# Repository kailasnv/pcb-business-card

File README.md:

# PCB Business Card

A creditcard sized custom PCB that doubles as a contact card and an interactive embedded demo. Designed from scratch, No dev board, no modules, bare chip bring up on a custom 2 layer board.

---

## What it does

| Mode | Trigger | Description |
|---|---|---|
| **Scroll** | Idle | Scrolls name and contact details across the 8×8 LED matrix |
| **Flappy Bird** | Button press | Classic Flappy Bird on an 8×8 grid |
| **Ball** | Tilt card | 1-pixel ball rolls around the matrix responding to physical tilt |

---

## Hardware

| Component | Part | Purpose |
|---|---|---|
| MCU | STM32G071RBT6 (LQFP-64) | Main processor, Cortex-M0+ @ 64MHz |
| LED Driver | MAX7219 (SOIC-24) | Drives 8×8 LED matrix over SPI |
| Display | 8×8 red LED matrix (0603 LEDs) | Output display |
| Accelerometer | IIS2DLPC (LGA-12) | 3-axis tilt sensing over I²C |
| Charger | TP4056 (SOP-8) | LiPo charging via USB-C |
| Regulator | MCP1700 | 3.3V LDO from LiPo |
| Power | 3.7V 1500mAh LiPo | Battery |
| Input | SMD tactile switch (3×6mm) | Game button |
| Connector | USB-C (16-pin SMD) | Charging input |

---

## Schematic overview

Five sub-circuits:
- **Power** — USB-C → TP4056 → LiPo → MCP1700 → 3.3V rail
- **MCU** — STM32G071RB with decoupling, BOOT0 pull-down, SWD pads
- **LED matrix** — MAX7219 driven over SPI, 64× 0603 LEDs in 8×8 grid
- **Accelerometer** — IIS2DLPC over I²C with additional INT1 interrupt line to MCU
- **Input** — Tactile button + 4-pad SWD debug port

---

###### Firmware (in progress)

---

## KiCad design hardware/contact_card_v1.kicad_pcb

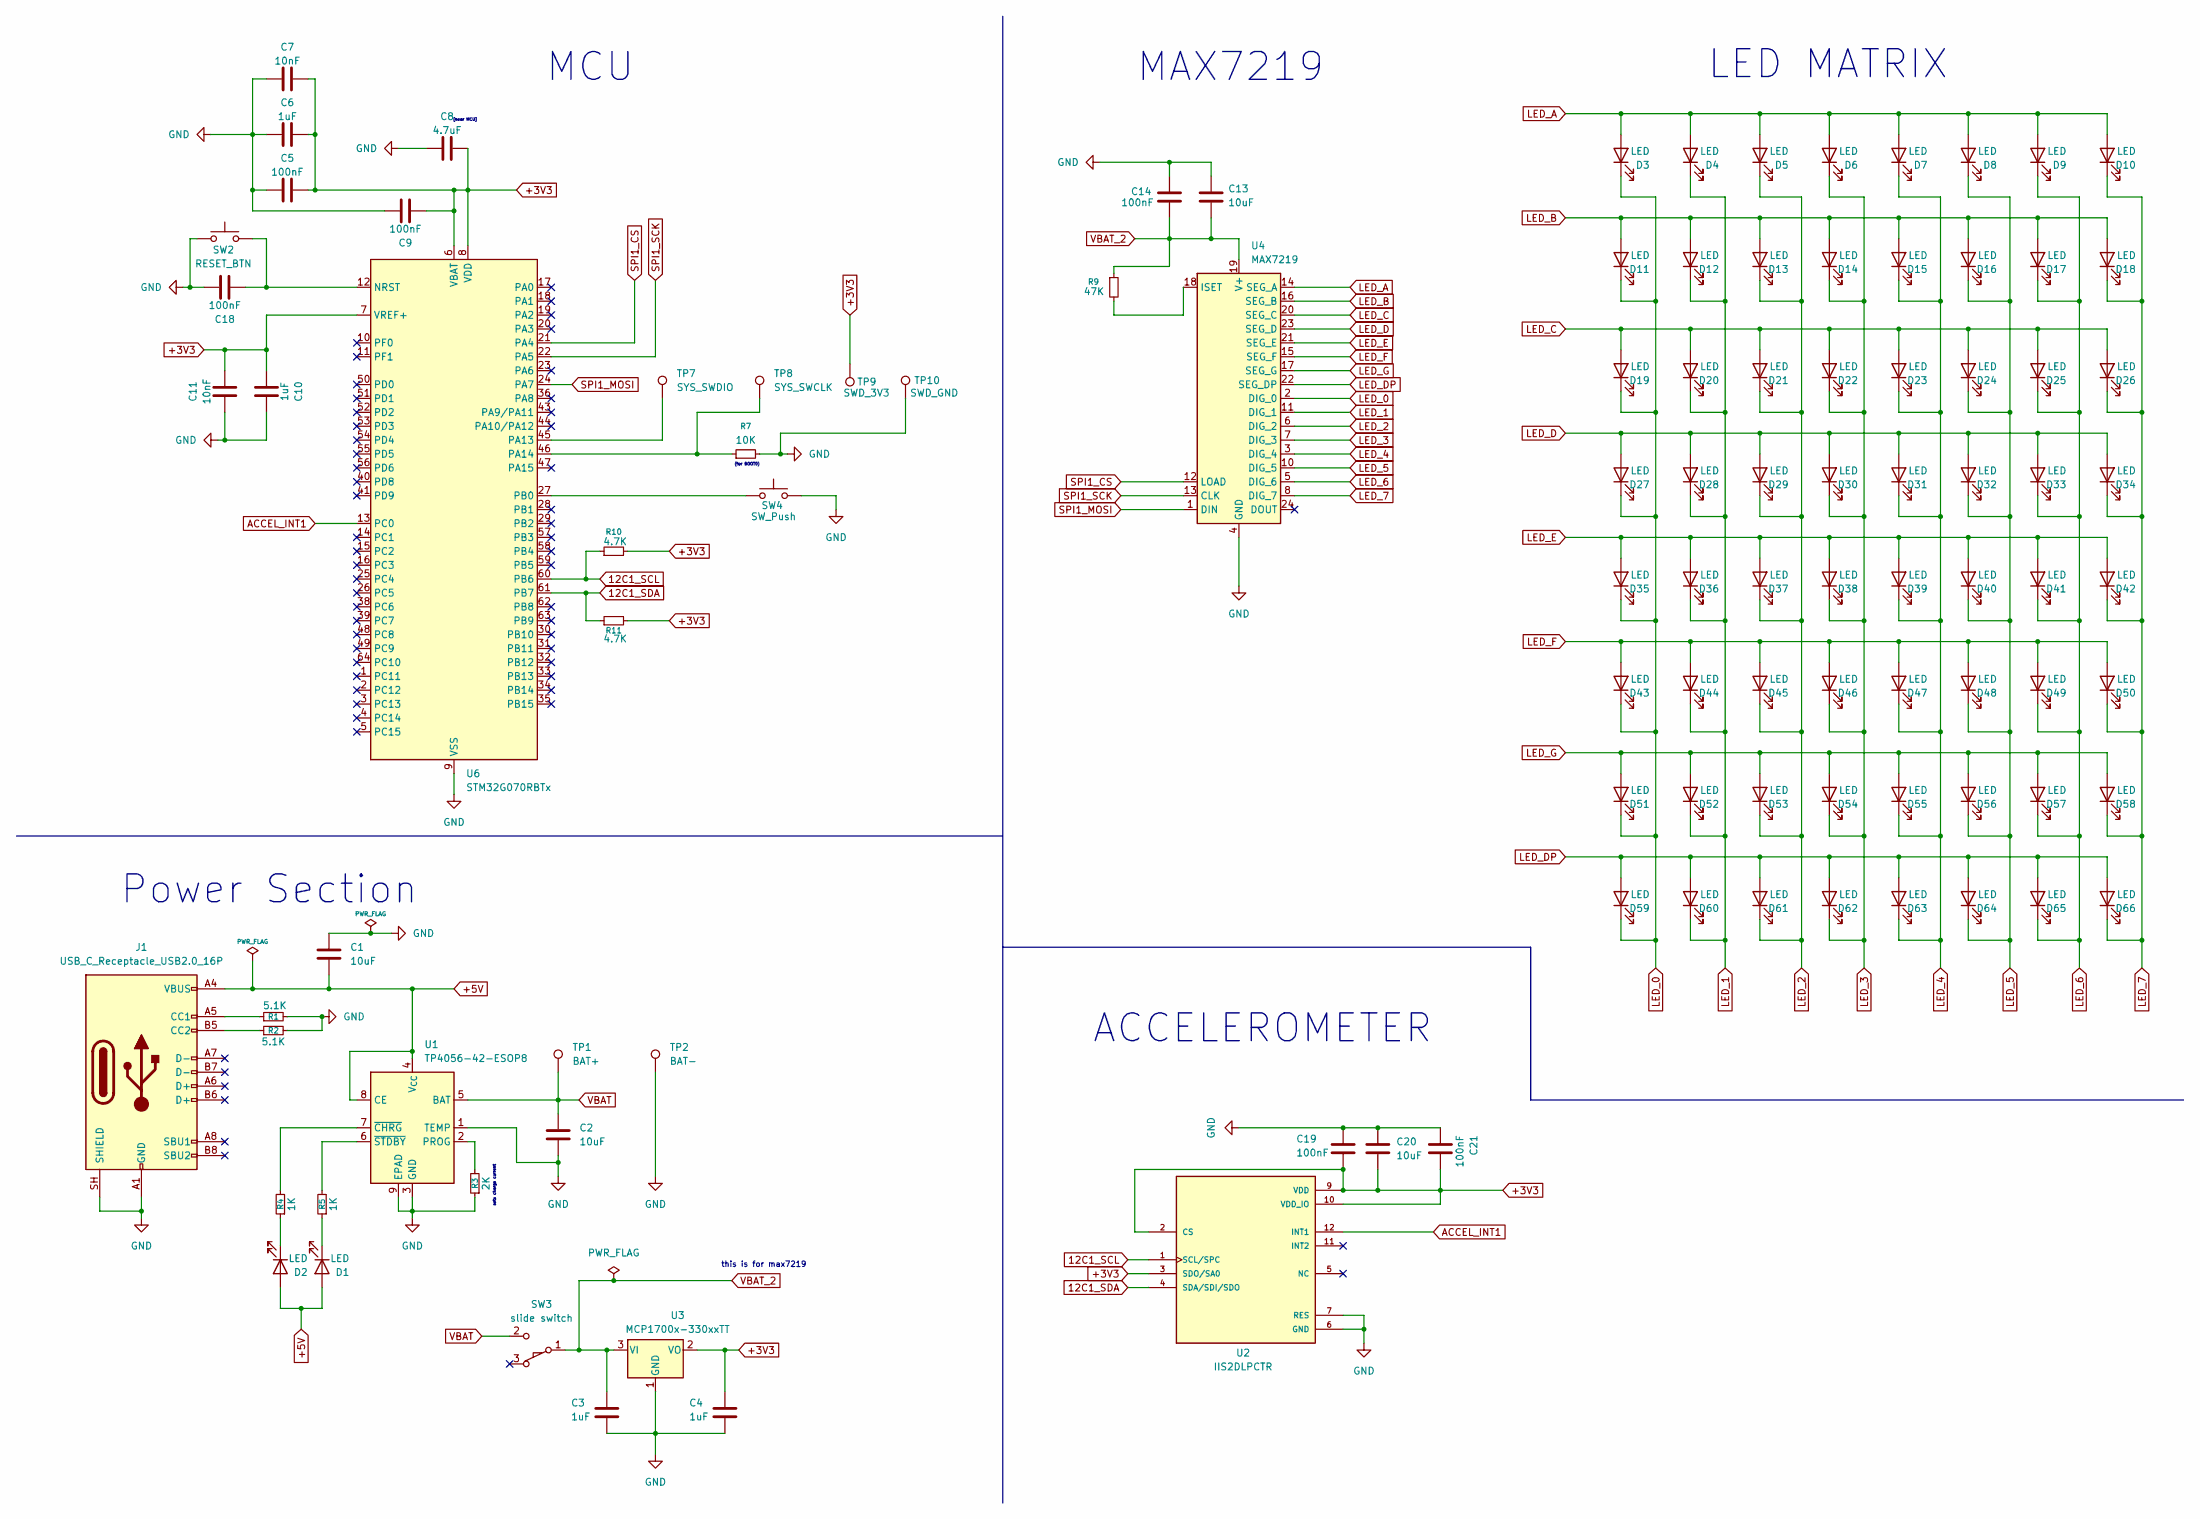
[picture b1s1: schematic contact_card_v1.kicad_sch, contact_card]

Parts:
C1, C2, C13, C20: 10uF; C_0402_1005Metric_Pad0.74x0.62mm_HandSolder
C3, C4, C6, C10: 1uF; C_0402_1005Metric_Pad0.74x0.62mm_HandSolder
C5, C9, C14, C18, C19, C21: 100nF; C_0603_1608Metric
C7, C11: 10nF; C_0603_1608Metric
C8: 4.7uF; C_0603_1608Metric
D1, D2, D3, D4, D5, D6, D7, D8, D9, D10, D11, D12, D13, D14, D15, D16, D17, D18, D19, D20, D21, D22, D23, D24, D25, D26, D27, D28, D29, D30, D31, D32, D33, D34, D35, D36, D37, D38, D39, D40, D41, D42, D43, D44, D45, D46, D47, D48, D49, D50, D51, D52, D53, D54, D55, D56, D57, D58, D59, D60, D61, D62, D63, D64, D65, D66: LED; LED_0603_1608Metric_Pad1.05x0.95mm_HandSolder
J1: USB_C_Receptacle_USB2.0_16P; USB_C_Receptacle_HRO_TYPE-C-31-M-12
R1, R2: 5.1K; R_0603_1608Metric_Pad0.98x0.95mm_HandSolder
R3: 2K; R_0603_1608Metric_Pad0.98x0.95mm_HandSolder
R4, R5: 1K; R_0603_1608Metric_Pad0.98x0.95mm_HandSolder
R7: 10K; R_0603_1608Metric_Pad0.98x0.95mm_HandSolder
R9: 47K; R_0603_1608Metric_Pad0.98x0.95mm_HandSolder
R10, R11: 4.7K; R_0603_1608Metric_Pad0.98x0.95mm_HandSolder
SW2: RESET_BTN; SW_Tactile_SPST_NO_Straight_CK_PTS636Sx25SMTRLFS
SW3: slide switch; SW_SPDT_PCM12
SW4: SW_Push; SW_Tactile_SPST_NO_Straight_CK_PTS636Sx25SMTRLFS
TP1: BAT+; TestPoint_Pad_2.0x2.0mm
TP2: BAT-; TestPoint_Pad_2.0x2.0mm
TP7: SYS_SWDIO; TestPoint_Pad_2.0x2.0mm
TP8: SYS_SWCLK; TestPoint_Pad_2.0x2.0mm
TP9: SWD_3V3; TestPoint_Pad_2.0x2.0mm
TP10: SWD_GND; TestPoint_Pad_2.0x2.0mm
U1: TP4056-42-ESOP8; SOIC-8-1EP_3.9x4.9mm_P1.27mm_EP2.29x3mm
U2: IIS2DLPCTR; LGA-12_2x2mm_P0.5mm; PARTREV 4
U3: MCP1700x-330xxTT; SOT-23
U4: MAX7219; SOIC-24W_7.5x15.4mm_P1.27mm
U6: STM32G070RBTx; LQFP-64_10x10mm_P0.5mm

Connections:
12C1_SCL: R10.1, U2.1 (SCL/SPC), U6.60 (PB6)
12C1_SDA: R11.1, U2.4 (SDA/SDI/SDO), U6.61 (PB7)
+3V3: C4.1, C5.2, C6.2, C7.2, C8.2, C9.1, C10.2, C11.1, C19.2, C20.2, C21.1, R10.2, R11.2, TP9.1 (1_1), U2.2 (CS), U2.3 (SDO/SA0), U2.9 (VDD), U2.10 (VDD_IO), U3.2 (VO), U6.6 (VBAT), U6.7 (VREF+), U6.8 (VDD)
+5V: C1.2, D1.2 (A), D2.2 (A), J1.A4 (VBUS), J1.A9 (VBUS), J1.B4 (VBUS), J1.B9 (VBUS), U1.4 (V_{CC}), U1.8 (CE)
ACCEL_INT1: U2.12 (INT1), U6.13 (PC0)
GND: C1.1, C2.2, C3.2, C4.2, C5.1, C6.1, C7.1, C8.1, C9.2, C10.1, C11.2, C13.1, C14.1, C18.2, C19.1, C20.1, C21.2, J1.A1 (GND), J1.A12 (GND), J1.B1 (GND), J1.B12 (GND), J1.SH (SHIELD), R1.2, R2.2, R3.1, R7.2, SW2.1, SW4.2, TP2.1 (1_1), TP10.1 (1_1), U1.1 (TEMP), U1.3 (GND), U1.9 (EPAD), U2.6 (GND), U2.7 (RES), U2.8 (GND), U3.1 (GND), U4.4 (GND), U4.9 (GND), U6.9 (VSS)
LED_0: D3.1 (K), D11.1 (K), D19.1 (K), D27.1 (K), D35.1 (K), D43.1 (K), D51.1 (K), D59.1 (K), U4.2 (DIG_0)
LED_1: D4.1 (K), D12.1 (K), D20.1 (K), D28.1 (K), D36.1 (K), D44.1 (K), D52.1 (K), D60.1 (K), U4.11 (DIG_1)
LED_2: D5.1 (K), D13.1 (K), D21.1 (K), D29.1 (K), D37.1 (K), D45.1 (K), D53.1 (K), D61.1 (K), U4.6 (DIG_2)
LED_3: D6.1 (K), D14.1 (K), D22.1 (K), D30.1 (K), D38.1 (K), D46.1 (K), D54.1 (K), D62.1 (K), U4.7 (DIG_3)
LED_4: D7.1 (K), D15.1 (K), D23.1 (K), D31.1 (K), D39.1 (K), D47.1 (K), D55.1 (K), D63.1 (K), U4.3 (DIG_4)
LED_5: D8.1 (K), D16.1 (K), D24.1 (K), D32.1 (K), D40.1 (K), D48.1 (K), D56.1 (K), D64.1 (K), U4.10 (DIG_5)
LED_6: D9.1 (K), D17.1 (K), D25.1 (K), D33.1 (K), D41.1 (K), D49.1 (K), D57.1 (K), D65.1 (K), U4.5 (DIG_6)
LED_7: D10.1 (K), D18.1 (K), D26.1 (K), D34.1 (K), D42.1 (K), D50.1 (K), D58.1 (K), D66.1 (K), U4.8 (DIG_7)
LED_A: D3.2 (A), D4.2 (A), D5.2 (A), D6.2 (A), D7.2 (A), D8.2 (A), D9.2 (A), D10.2 (A), U4.14 (SEG_A)
LED_B: D11.2 (A), D12.2 (A), D13.2 (A), D14.2 (A), D15.2 (A), D16.2 (A), D17.2 (A), D18.2 (A), U4.16 (SEG_B)
LED_C: D19.2 (A), D20.2 (A), D21.2 (A), D22.2 (A), D23.2 (A), D24.2 (A), D25.2 (A), D26.2 (A), U4.20 (SEG_C)
LED_D: D27.2 (A), D28.2 (A), D29.2 (A), D30.2 (A), D31.2 (A), D32.2 (A), D33.2 (A), D34.2 (A), U4.23 (SEG_D)
LED_DP: D59.2 (A), D60.2 (A), D61.2 (A), D62.2 (A), D63.2 (A), D64.2 (A), D65.2 (A), D66.2 (A), U4.22 (SEG_DP)
LED_E: D35.2 (A), D36.2 (A), D37.2 (A), D38.2 (A), D39.2 (A), D40.2 (A), D41.2 (A), D42.2 (A), U4.21 (SEG_E)
LED_F: D43.2 (A), D44.2 (A), D45.2 (A), D46.2 (A), D47.2 (A), D48.2 (A), D49.2 (A), D50.2 (A), U4.15 (SEG_F)
LED_G: D51.2 (A), D52.2 (A), D53.2 (A), D54.2 (A), D55.2 (A), D56.2 (A), D57.2 (A), D58.2 (A), U4.17 (SEG_G)
unnamed: D1.1 (K), R5.1
unnamed: D2.1 (K), R4.1
unnamed: J1.A5 (CC1), R1.1
unnamed: J1.B5 (CC2), R2.1
unnamed: R3.2, U1.2 (PROG)
unnamed: R4.2, U1.7 (~CHRG)
unnamed: R5.2, U1.6 (~STDBY)
unnamed: R9.2, U4.18 (ISET)
unnamed: C18.1, SW2.2, U6.12 (NRST)
unnamed: TP7.1 (1_1), U6.45 (PA13)
unnamed: R7.1, TP8.1 (1_1), U6.46 (PA14)
unnamed: SW4.1, U6.27 (PB0)
SPI1_CS: U4.12 (LOAD), U6.21 (PA4)
SPI1_MOSI: U4.1 (DIN), U6.24 (PA7)
SPI1_SCK: U4.13 (CLK), U6.22 (PA5)
VBAT: C2.1, SW3.2 (B), TP1.1 (1_1), U1.5 (BAT)
VBAT_2: C3.1, C13.2, C14.2, R9.1, SW3.1 (A), U3.3 (VI), U4.19 (V+)

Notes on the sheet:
[near MCU]
sets charge current
LED MATRIX
MCU
MAX7219
Power Section
this is for max7219
(for BOOT0)
ACCELEROMETER

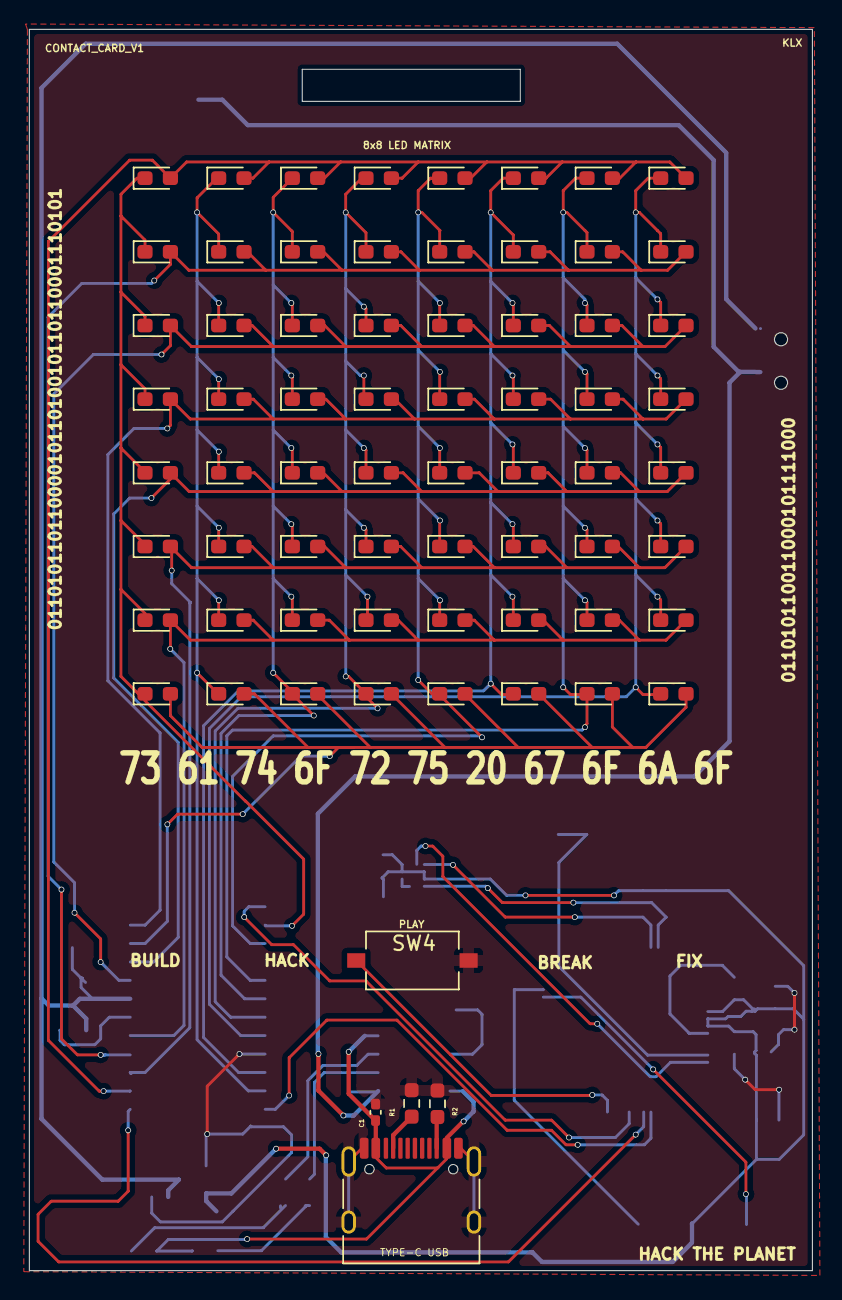
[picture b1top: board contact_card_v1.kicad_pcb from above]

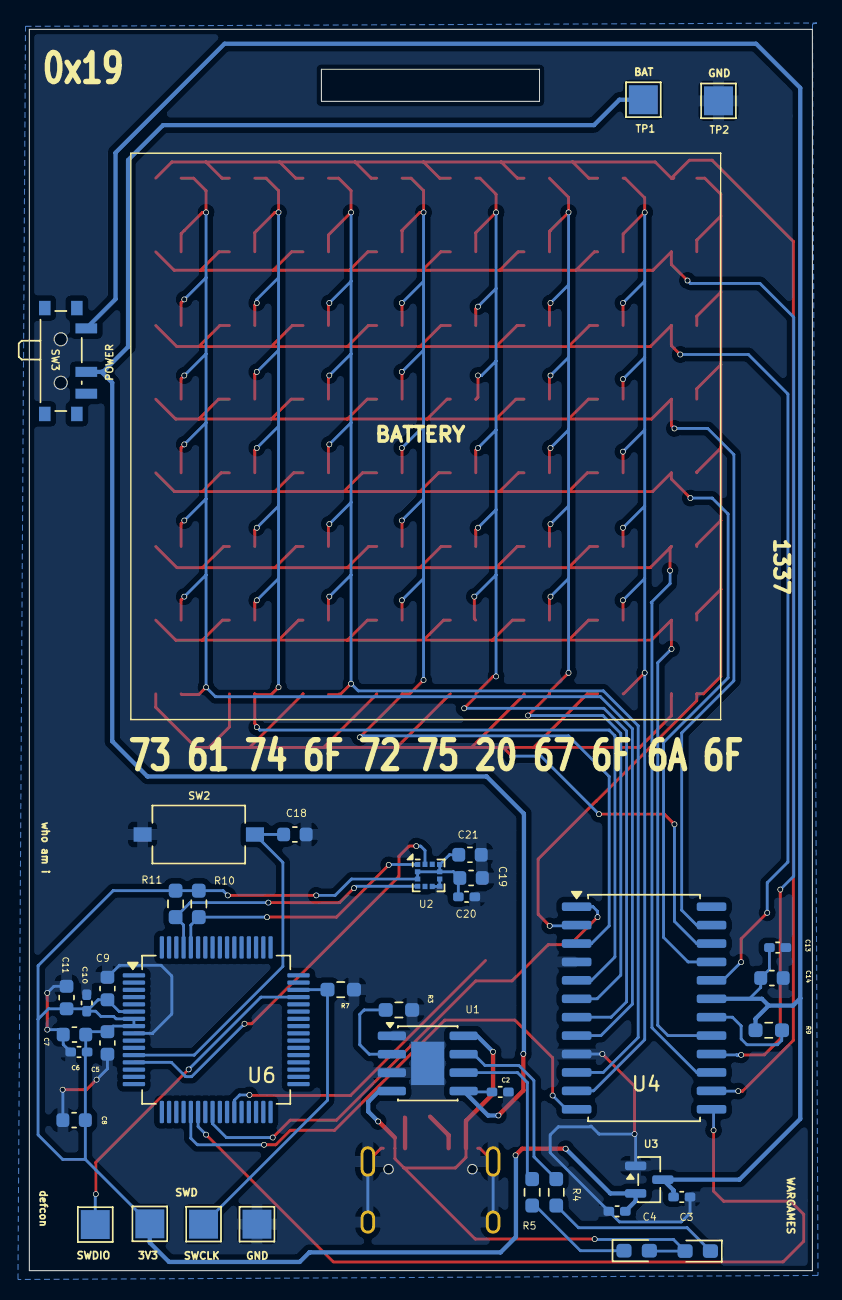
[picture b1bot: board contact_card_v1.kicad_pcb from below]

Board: 2 copper layers, 54.0 x 85.6 mm, 107 parts (38 on the bottom side), 39 nets.
